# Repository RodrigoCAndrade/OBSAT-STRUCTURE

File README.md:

<div align="center">
  
</div>

<h1 align="center">OBSAT Structure</h1>

<p align="center">

</p>

<br>

## Overview

This project presents the development of a 1U CubeSat structure designed to support the AXISS architecture and remain compatible with the Brazilian Satellite Olympiad (OBSAT). The mechanical design focuses on standard CubeSat integration, robust packaging of onboard subsystems, secure launch deployment interfaces, and practical manufacturing constraints for educational and mission-focused use.

**Technical Parameters**

* Form factor: 1U CubeSat
* OBSAT compatibility: Mechanical and interface constraints aligned with the competition requirements
* Primary focus: Structural integrity, subsystem accommodation, and launch survivability
* Integration: Standard CubeSat external envelope, without rails, and internal mounting references

## Repository Organization

* `docs`: Requirements, mission assumptions, and interface control documentation.
* `mechanics`: 3D models, technical drawings, and physical integration constraints for the 1U structure.
* `simulations`: Thermal, vibration, and structural analyses.
* `verification`: Test plans, laboratory procedures, and validation reports for OBSAT-oriented compliance.

## Releases

<table>
  <thead>
    <tr>
      <th>Render</th>
      <th>Hardware Revision</th>
      <th>Status</th>
      <th>Latest Release</th>
      <th>Date</th>
      <th>Datasheet</th>
      <th>BOM</th>
      <th>Manufacturing Info</th>
    </tr>
  </thead>
  <tbody>
    <tr>
      <td></td>
      <td>1U Structure v1</td>
      <td>Testing</td>
      <td><a href="#">v1.0</a></td>
      <td>2026-08-04</td>
      <td><a href="#">PDF</a></td>
      <td>Available</td>
      <td><a href="#">Manufacturing Package</a></td>
    </tr>
  </tbody>
</table>

## Contributing

We welcome contributions to this project. To keep the mechanical design aligned with our aerospace engineering standards and OBSAT compatibility goals, please review our [Contribution Guidelines](CONTRIBUTING.md) before opening issues, modifying the structure, or submitting pull requests.

## References

This project builds upon the structural and integration concepts developed by the AXISS engineering team. It follows CubeSat best practices and is intended to support educational and mission-oriented development within the OBSAT ecosystem.

**Associated Missions**

<p>
  
</p>

## License

The structural design, mechanical drawings, and related hardware documentation are licensed under the permissive **[CERN-OHL-P-2.0](mechanics/LICENSE)** open-hardware license. You may use, modify, distribute, and commercialize the design subject to the terms of that license.

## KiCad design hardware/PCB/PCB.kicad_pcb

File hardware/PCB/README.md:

<div align="center">
  
</div>

<h1 align="center">Native KiCad Project</h1>

<p align="center">
  <em>Source files for the hardware project (.kicad_pro, .kicad_sch, .kicad_pcb).</em>
</p>

<br>

### What you will find here
- Electronic schematics.
- Printed Circuit Board (PCB) layout.
- Stackup definitions and design rules.

### Guidelines
> Before opening a Pull Request, ensure that the DRC (Design Rule Check) and ERC (Electrical Rule Check) run without errors.

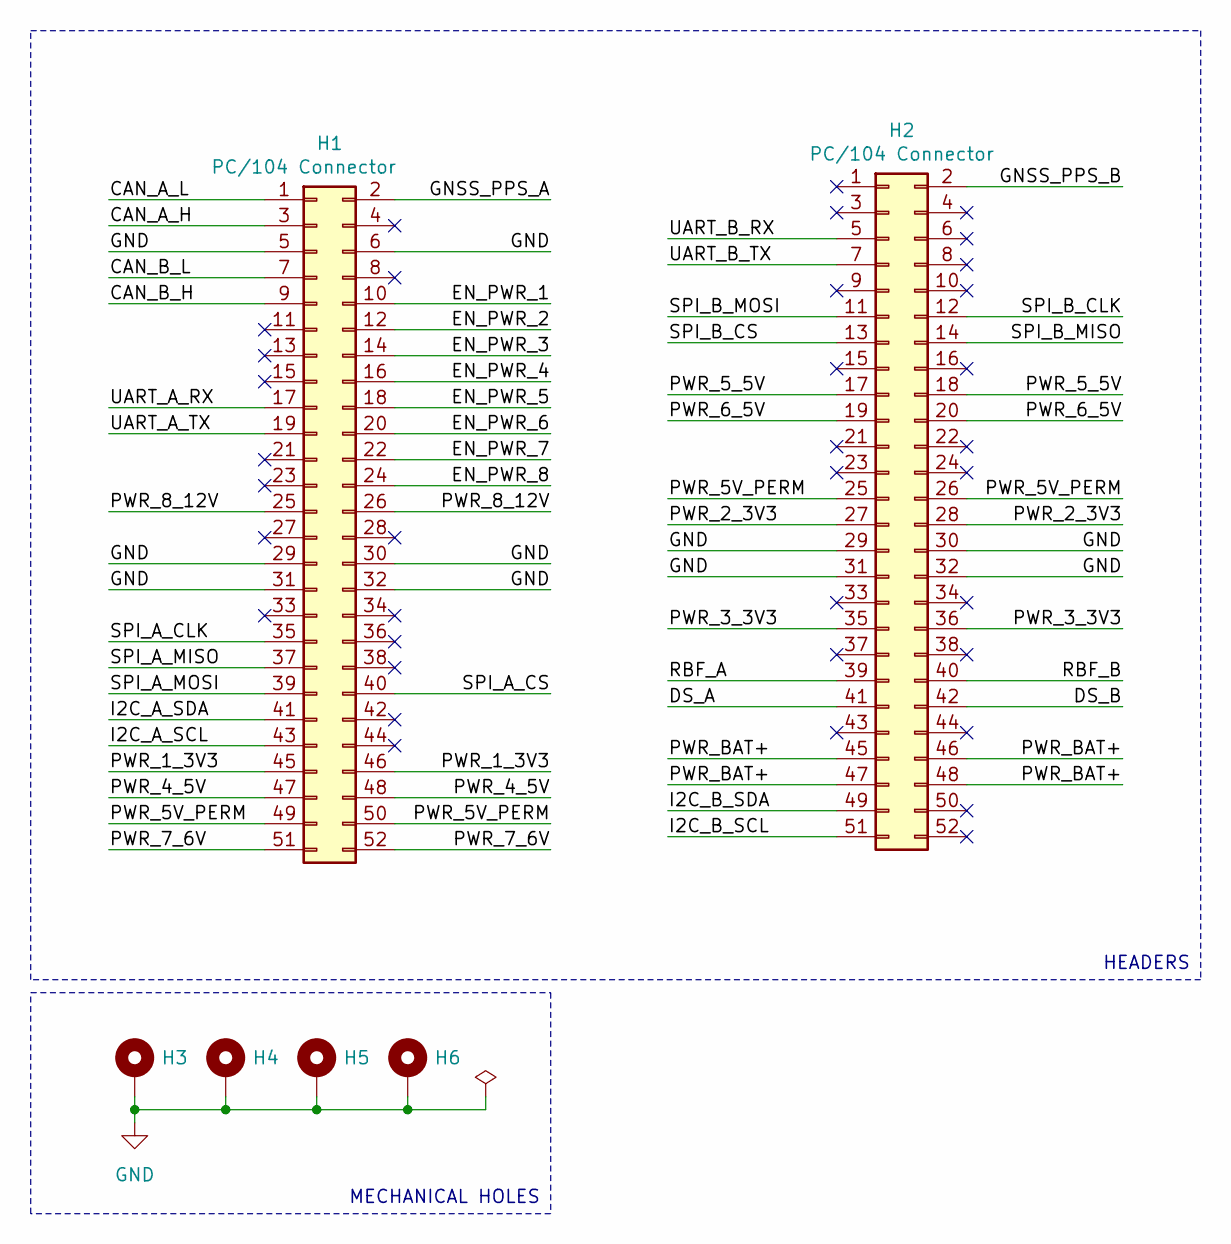
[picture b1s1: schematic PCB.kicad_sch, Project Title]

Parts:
H1, H2: PC/104 Connector; PinSocket_2x26_P2.54mm_Vertical
H3, H4, H5, H6: MountingHole_Pad; MountingHole_3.2mm_M3_Pad_Via

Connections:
/CAN_A_H: H1.3
/CAN_A_L: H1.1
/CAN_B_H: H1.9
/CAN_B_L: H1.7
/DS_A: H2.41
/DS_B: H2.42
/EN_PWR_1: H1.10
/EN_PWR_2: H1.12
/EN_PWR_3: H1.14
/EN_PWR_4: H1.16
/EN_PWR_5: H1.18
/EN_PWR_6: H1.20
/EN_PWR_7: H1.22
/EN_PWR_8: H1.24
/GNSS_PPS_A: H1.2
/GNSS_PPS_B: H2.2
/I2C_A_SCL: H1.43
/I2C_A_SDA: H1.41
/I2C_B_SCL: H2.51
/I2C_B_SDA: H2.49
/PWR_1_3V3: H1.45, H1.46
/PWR_2_3V3: H2.27, H2.28
/PWR_3_3V3: H2.35, H2.36
/PWR_4_5V: H1.47, H1.48
/PWR_5V_PERM: H1.49, H1.50, H2.25, H2.26
/PWR_5_5V: H2.17, H2.18
/PWR_6_5V: H2.19, H2.20
/PWR_7_6V: H1.51, H1.52
/PWR_8_12V: H1.25, H1.26
/PWR_BAT+: H2.45, H2.46, H2.47, H2.48
/RBF_A: H2.39
/RBF_B: H2.40
/SPI_A_CLK: H1.35
/SPI_A_CS: H1.40
/SPI_A_MISO: H1.37
/SPI_A_MOSI: H1.39
/SPI_B_CLK: H2.12
/SPI_B_CS: H2.13
/SPI_B_MISO: H2.14
/SPI_B_MOSI: H2.11
/UART_A_RX: H1.17
/UART_A_TX: H1.19
/UART_B_RX: H2.5
/UART_B_TX: H2.7
GND: H1.5, H1.6, H1.29, H1.30, H1.31, H1.32, H2.29, H2.30, H2.31, H2.32, H3.1 (1_1), H4.1 (1_1), H5.1 (1_1), H6.1 (1_1)

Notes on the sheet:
MECHANICAL HOLES
HEADERS

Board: 2 copper layers, 6 parts (0 on the bottom side), 11 nets, no tracks yet.
